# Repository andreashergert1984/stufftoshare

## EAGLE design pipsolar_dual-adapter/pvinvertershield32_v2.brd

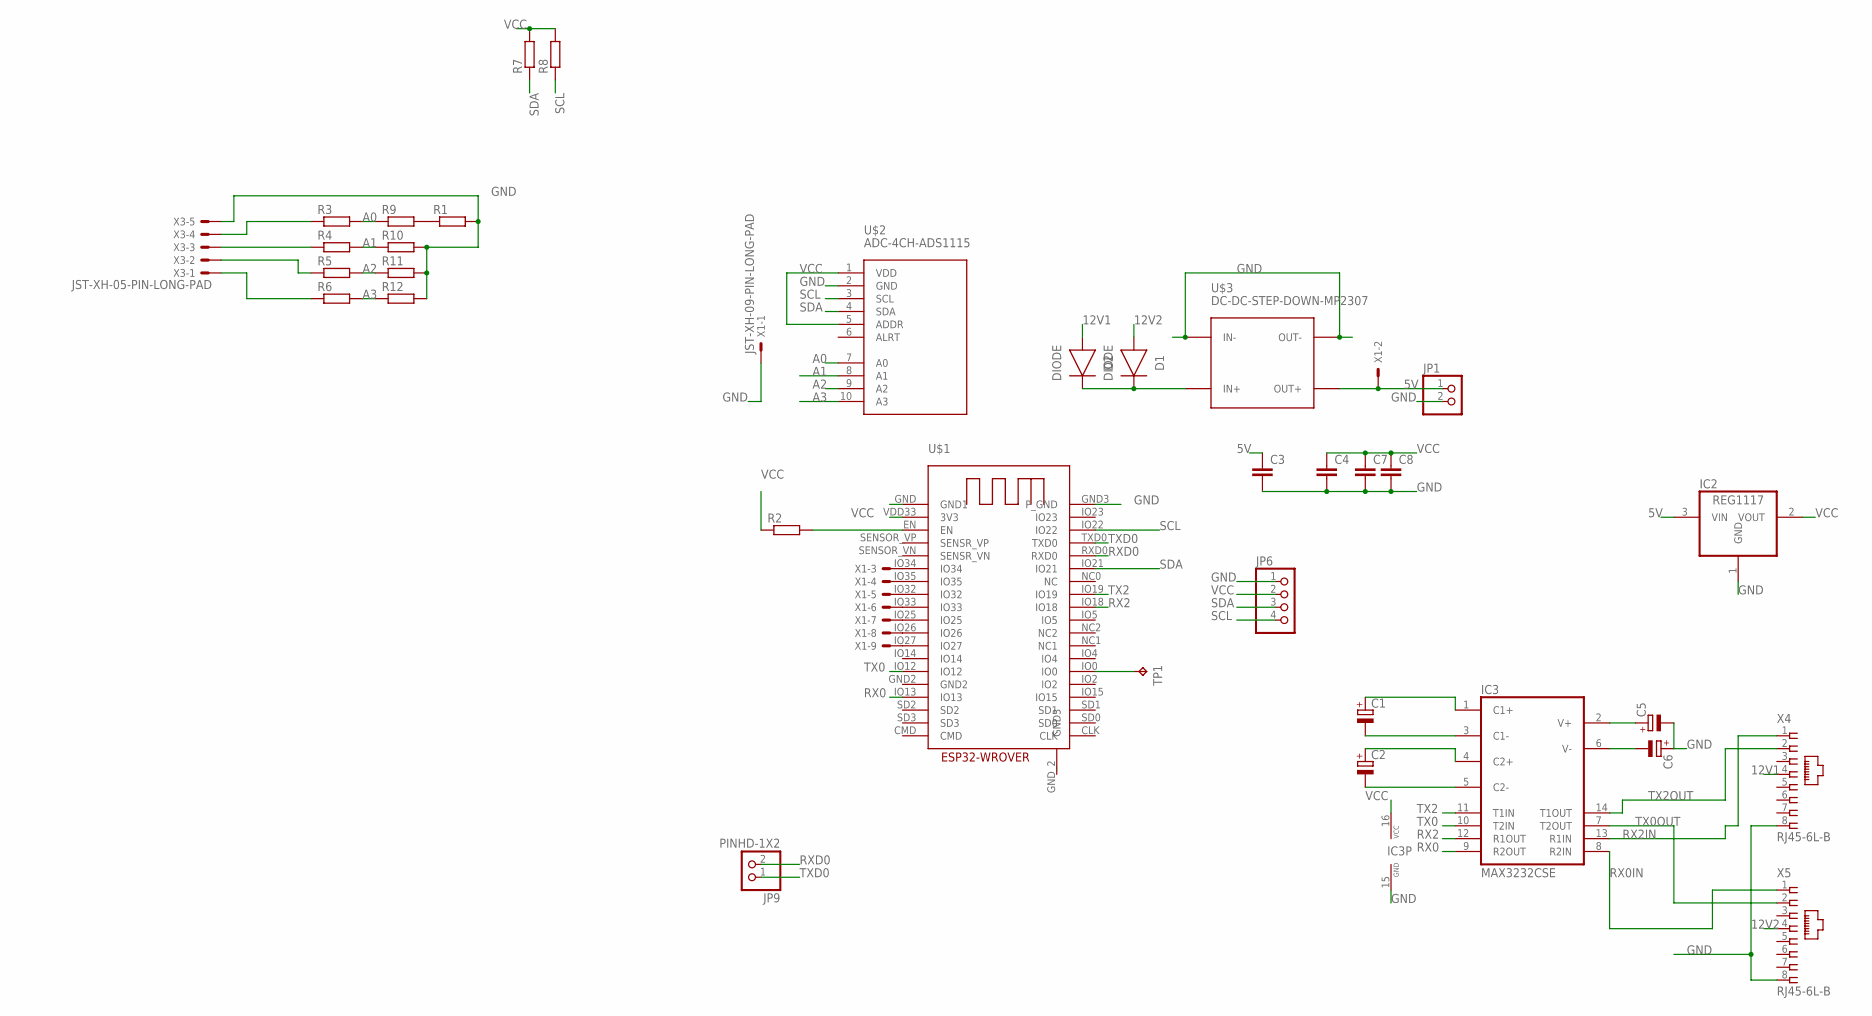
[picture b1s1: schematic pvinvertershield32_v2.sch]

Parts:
C1, C2, C5, C6: CPOL-EUE2.5-6; E2,5-6
C3, C4, C7, C8: C-EUC1210; C1210
D1, D2: DIODE; DIOMELF5024
IC2: REG1117; SOT223
IC3: MAX3232CSE; SO16
JP1, JP9: PINHD-1X2; 1X02
JP6: PINHD-1X4; 1X04
R1, R2, R3, R4, R5, R6, R9, R10, R11, R12: R-EU_R0805; R0805
R7, R8: R-EU_0207/10; 0207/10
TP1: TPB2,54; B2,54
U$1: ESP32-WROVER
U$2: ADC-4CH-ADS1115
U$3: DC-DC-STEP-DOWN-MP2307
X1: JST-XH-09-PIN-LONG-PAD; JST-XH-09-PACKAGE-LONG-PAD
X3: JST-XH-05-PIN-LONG-PAD; JST-XH-05-PACKAGE-LONG-PAD
X4, X5: RJ45-6L-B; RJ45-NO-SHIELD

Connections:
5V: C3.1, IC2.3 (VIN), JP1.1, U$3.OUT+, X1.2
12V1: D2.2 (A), X4.4
12V2: D1.2 (A), X5.4
A0: R3.2, R9.1, U$2.7 (A0)
A1: R4.2, R10.1, U$2.8 (A1)
A2: R5.2, R11.1, U$2.9 (A2)
A3: R6.2, R12.1, U$2.10 (A3)
GND: C3.2, C4.2, C5.-, C6.+, C7.2, C8.2, IC2.1 (GND), IC3.15 (GND), JP1.2, JP6.1, R1.2, R10.2, R11.2, R12.2, U$1.GND (GND1), U$1.GND3 (P_GND), U$2.2 (GND), U$3.IN-, U$3.OUT-, X1.1, X3.5, X4.8, X5.8
unnamed: C1.+, IC3.1 (C1+)
unnamed: C1.-, IC3.3 (C1-)
unnamed: C2.+, IC3.4 (C2+)
unnamed: C2.-, IC3.5 (C2-)
unnamed: C5.+, IC3.2 (V+)
unnamed: C6.-, IC3.6 (V-)
unnamed: D1.1 (C), D2.1 (C), U$3.IN+
unnamed: U$1.IO34, X1.3
unnamed: R1.1, R9.2
unnamed: U$1.IO35, X1.4
unnamed: R3.1, X3.4
unnamed: R4.1, X3.3
unnamed: U$1.IO32, X1.5
unnamed: R2.2, U$1.EN
unnamed: U$1.IO33, X1.6
unnamed: U$1.IO25, X1.7
unnamed: U$1.IO26, X1.8
unnamed: R5.1, X3.2
unnamed: R6.1, X3.1
unnamed: U$1.IO27, X1.9
unnamed: TP1.TP, U$1.IO0
RX0: IC3.9 (R2OUT), U$1.IO13
RX0IN: IC3.8 (R2IN), X5.1
RX2: IC3.12 (R1OUT), U$1.IO18
RX2IN: IC3.13 (R1IN), X4.1
RXD0: JP9.2, U$1.RXD0
SCL: JP6.4, R8.1, U$1.IO22, U$2.3 (SCL)
SDA: JP6.3, R7.1, U$1.IO21, U$2.4 (SDA)
TX0: IC3.10 (T2IN), U$1.IO12
TX0OUT: IC3.7 (T2OUT), X5.2
TX2: IC3.11 (T1IN), U$1.IO19
TX2OUT: IC3.14 (T1OUT), X4.2
TXD0: JP9.1, U$1.TXD0
VCC: C4.1, C7.1, C8.1, IC2.2 (VOUT), IC3.16 (VCC), JP6.2, R2.1, R7.2, R8.2, U$1.VDD33 (3V3), U$2.1 (VDD), U$2.5 (ADDR)

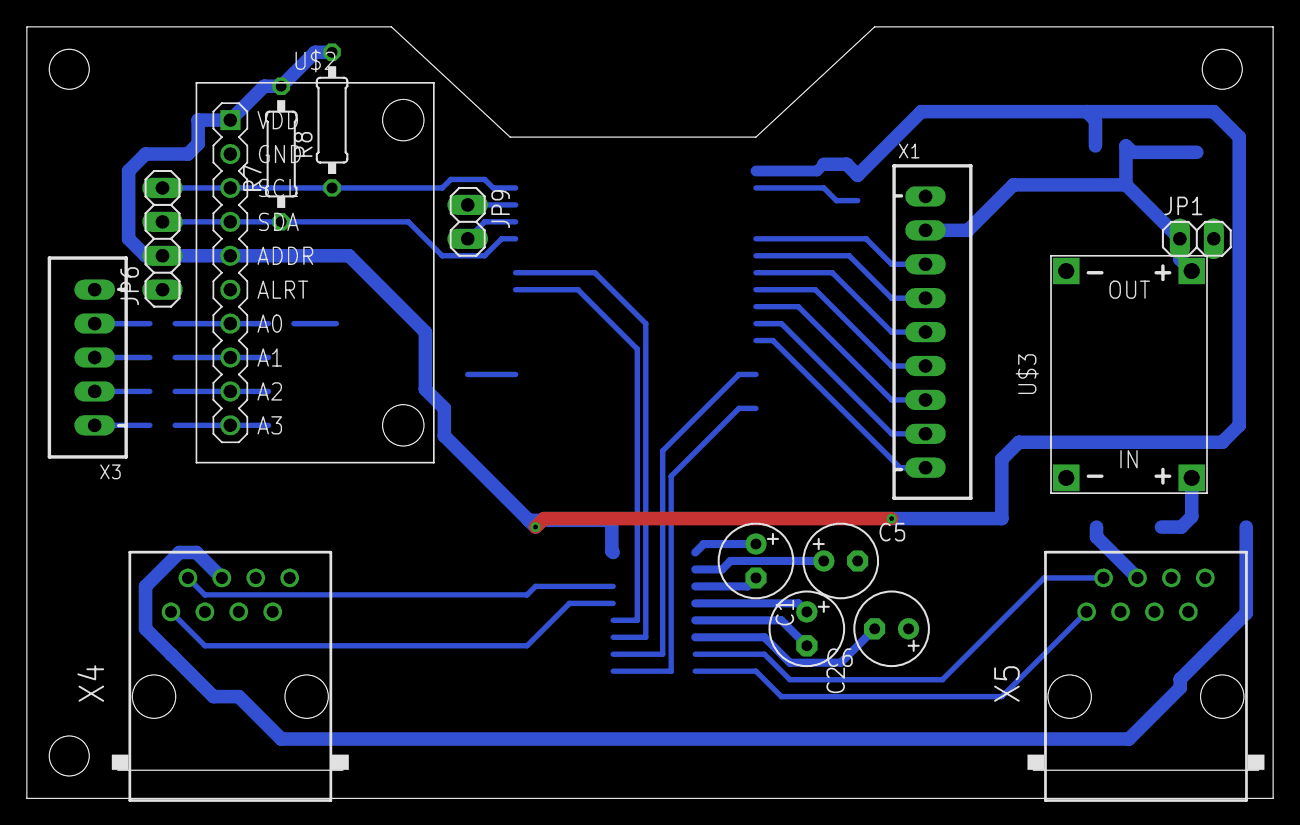
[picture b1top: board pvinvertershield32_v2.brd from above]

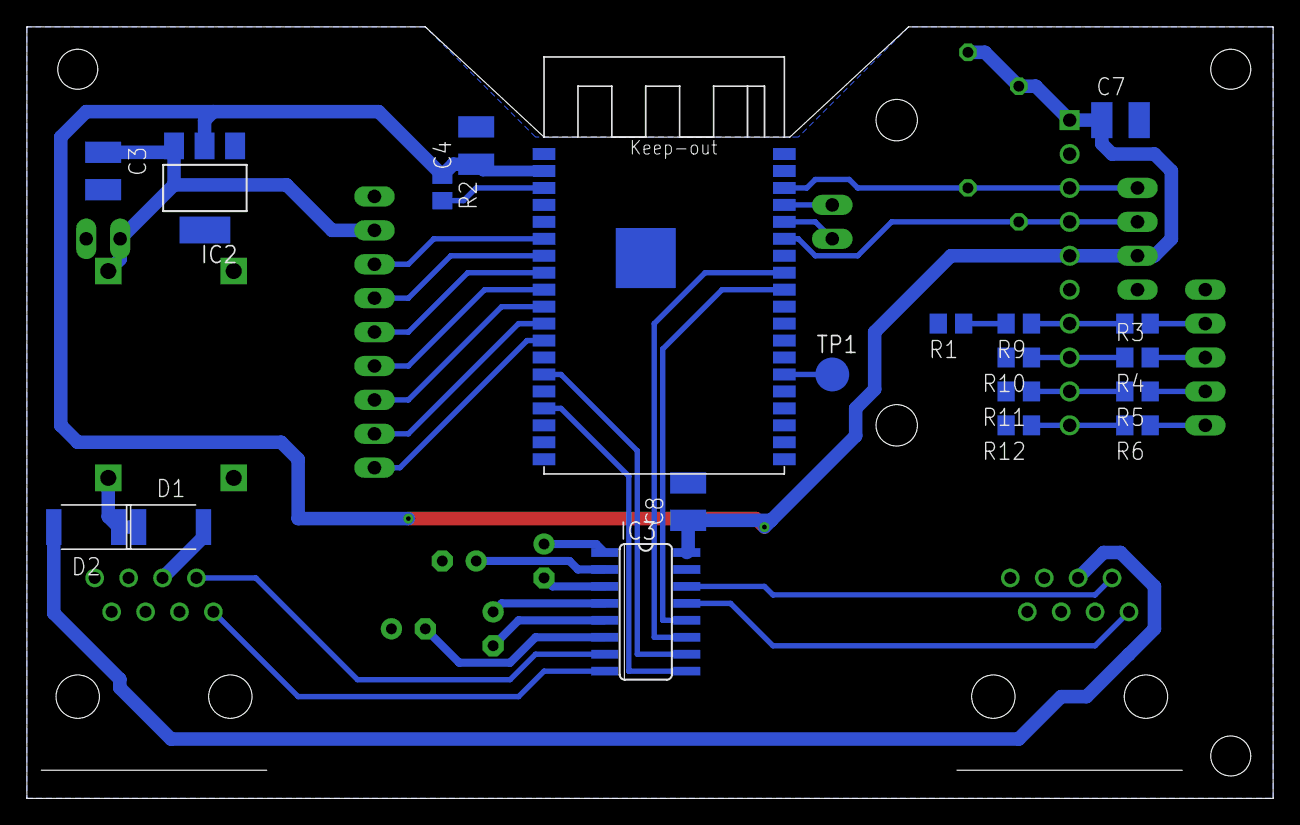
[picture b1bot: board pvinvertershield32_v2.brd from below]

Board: 2 copper layers, 93.3 x 57.8 mm, 35 parts (20 on the bottom side), 42 nets.

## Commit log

2021-10-03 init

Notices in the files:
parts and their libraries:
diy-modules: Released under the Creative Commons Attribution 4.0 International License: http://creativecommons.org/licenses/by/4.0
